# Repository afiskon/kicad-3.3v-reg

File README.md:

# kicad-3.3v-reg
My first PCB designed in KiCad

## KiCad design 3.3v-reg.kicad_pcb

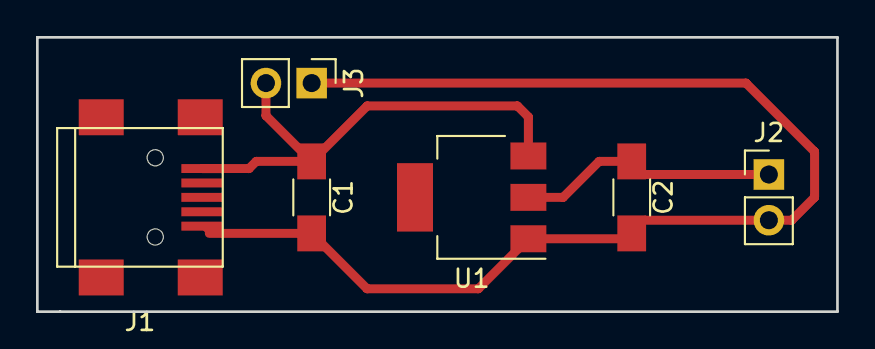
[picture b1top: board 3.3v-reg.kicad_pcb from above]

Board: 2 copper layers, 44.5 x 15.2 mm, 6 parts (0 on the bottom side), 3 nets.

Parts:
C1, C2: C; C_1206_HandSoldering
J1: USB_OTG; USB_Mini-B
J2, J3: Conn_01x02; Pin_Header_Straight_1x02_Pitch2.54mm
U1: AP1117-33; SOT-223-3_TabPin2

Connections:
+3V3: C2.1, J2.1, U1.2
GND: C1.2, C2.2, J1.5, J2.2, J3.1, U1.1
unnamed: C1.1, J1.1, J3.2, U1.3

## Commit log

2017-11-18 Moved from a sandbox repository
2018-01-12 Add Edge.Cuts layer
